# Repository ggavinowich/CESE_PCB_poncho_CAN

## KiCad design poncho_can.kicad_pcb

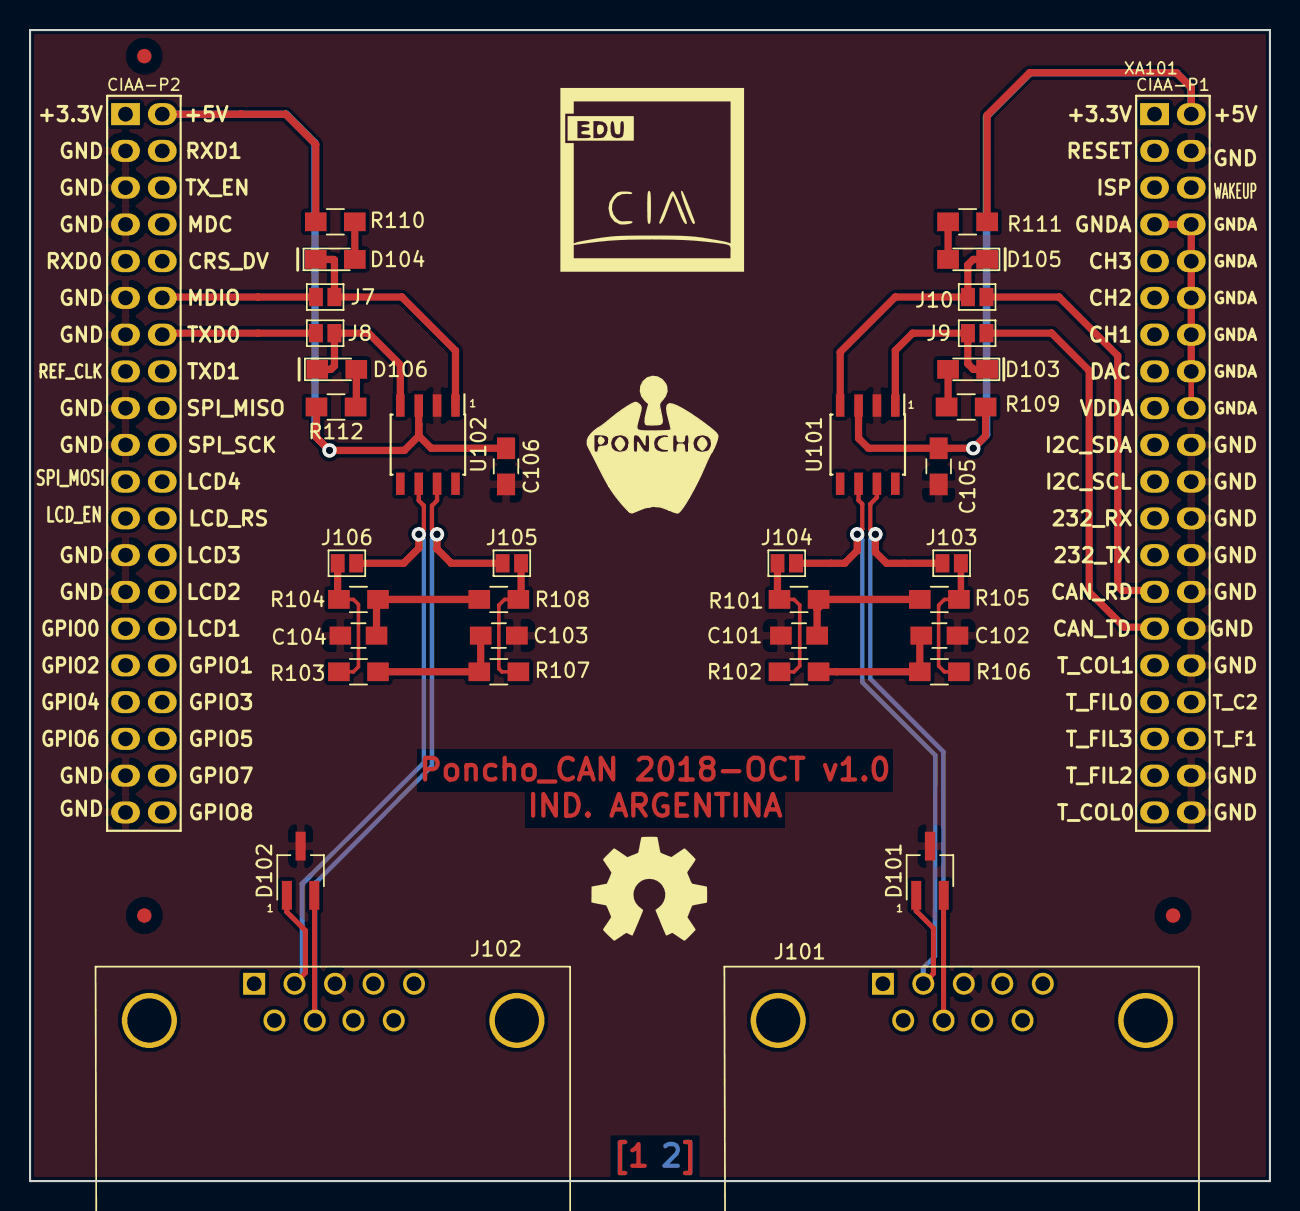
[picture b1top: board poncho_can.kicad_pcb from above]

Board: 2 copper layers, 85.7 x 79.6 mm, 41 parts (0 on the bottom side), 28 nets.

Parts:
C101, C102, C103, C104: 47n; C_0805_HandSoldering
C105, C106: 100n; C_0805_HandSoldering
D101, D102: RSB27C2; SOT-23W_Handsoldering
D103, D106: LED_RX; LED_0805_HandSoldering
D104, D105: LED_TX; LED_0805_HandSoldering
F101, F102, F103: Fiduciaria; Fiducial_1mm_Dia_2.54mm_Outer_CopperBottom
G101: Logo_OSHWA
J7, J8, J9, J10, J103, J104, J105, J106: GS2
J101, J102: DB9_Male_MountingHoles; DB9MC
R101, R102, R103, R104, R105, R106, R107, R108: 60; R_0805_HandSoldering
R109, R110, R111, R112: 270; R_0805_HandSoldering
U101, U102: TJA1051T; SOIC-8_3.9x4.9mm_Pitch1.27mm
XA101: Conn_Poncho2P_2x_20x2; Conn_Poncho_SinBorde

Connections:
+5V: C105.1, R109.2, R111.2, U101.3, XA101.2
+5VP: C106.1, R110.2, R112.2, U102.3, XA101.42
/CAN1+: D101.2, J101.7, J103.1, U101.7
/CAN1-: D101.1, J101.2, J104.2, U101.6
/CAN2+: D102.2, J102.7, J105.1, U102.7
/CAN2-: D102.1, J102.2, J106.2, U102.6
GND: C101.1, C102.2, C103.1, C104.2, C105.2, C106.2, D101.3, D102.3, J101.3, J102.3, U101.2, U102.2, XA101.4, XA101.20, XA101.22, XA101.24, XA101.26, XA101.28, XA101.30, XA101.32, XA101.38, XA101.40, XA101.43, XA101.45, XA101.47, XA101.51, XA101.53, XA101.57, XA101.59, XA101.65, XA101.67, XA101.77, XA101.79
GNDA: XA101.7, XA101.8, XA101.10, XA101.12, XA101.14, XA101.16, XA101.18
unnamed: C101.2, R101.1, R105.2
unnamed: C102.1, R102.1, R106.2
unnamed: C103.2, R103.1, R107.2
unnamed: C104.1, R104.1, R108.2
unnamed: D103.1, J9.2, U101.1
unnamed: D103.2, R109.1
unnamed: D104.1, J7.2, U102.1
unnamed: D104.2, R110.1
unnamed: D105.1, J10.2, U101.4
unnamed: D105.2, R111.1
unnamed: D106.1, J8.2, U102.4
unnamed: D106.2, R112.1
unnamed: J7.1, XA101.52
unnamed: J8.1, XA101.54
unnamed: J9.1, XA101.29
unnamed: J10.1, XA101.27
unnamed: J103.2, R105.1, R106.1
unnamed: J104.1, R101.2, R102.2
unnamed: J105.2, R107.1, R108.1
unnamed: J106.1, R103.2, R104.2

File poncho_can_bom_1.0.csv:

Component,Description,Part,References,Value,Footprint,Quantity Per PCB,Datasheet,Digikey Part Number,Manf#,Digikey#,Manf
1,,C,C105,100n,C_0805_HandSoldering,1,,311-4354-1-ND,,,
2,,C,C106,100n,C_0805_HandSoldering,1,,311-4354-1-ND,,,
3,,C,C101,47n,C_0805_HandSoldering,1,,490-7227-1-ND,,,
4,,C,C102,47n,C_0805_HandSoldering,1,,490-7227-1-ND,,,
5,,C,C103,47n,C_0805_HandSoldering,1,,490-7227-1-ND,,,
6,,C,C104,47n,C_0805_HandSoldering,1,,490-7227-1-ND,,,
7,,LED_ALT,D103,LED_RX,LED_0805_HandSoldering,1,,160-1427-1-ND,,,
8,,LED_ALT,D106,LED_RX,LED_0805_HandSoldering,1,,160-1427-1-ND,,,
9,,LED_ALT,D104,LED_TX,LED_0805_HandSoldering,1,,160-1423-1-ND,,,
10,,LED_ALT,D105,LED_TX,LED_0805_HandSoldering,1,,160-1423-1-ND,,,
11,,A00094,D101,RSB27C2,SOT-23W_Handsoldering,1,,ESD7002WTT1GOSCT-ND,,,
12,,A00094,D102,RSB27C2,SOT-23W_Handsoldering,1,,ESD7002WTT1GOSCT-ND,,,
13,,GS2,J10,GS2,GS2,1,,,,,
14,,GS2,J103,GS2,GS2,1,,,,,
15,,GS2,J104,GS2,GS2,1,,,,,
16,,GS2,J105,GS2,GS2,1,,,,,
17,,GS2,J106,GS2,GS2,1,,,,,
18,,GS2,J7,GS2,GS2,1,,,,,
19,,GS2,J8,GS2,GS2,1,,,,,
20,,GS2,J9,GS2,GS2,1,,,,,
21,,R,R109,270,R_0805_HandSoldering,1,,RMCF0805JT270RCT-ND,,,
22,,R,R110,270,R_0805_HandSoldering,1,,RMCF0805JT270RCT-ND,,,
23,,R,R111,270,R_0805_HandSoldering,1,,RMCF0805JT270RCT-ND,,,
24,,R,R112,270,R_0805_HandSoldering,1,,RMCF0805JT270RCT-ND,,,
25,,R,R101,60,R_0805_HandSoldering,1,,RMCF0805FT60R4CT-ND,,,
26,,R,R102,60,R_0805_HandSoldering,1,,RMCF0805FT60R4CT-ND,,,
27,,R,R103,60,R_0805_HandSoldering,1,,RMCF0805FT60R4CT-ND,,,
28,,R,R104,60,R_0805_HandSoldering,1,,RMCF0805FT60R4CT-ND,,,
29,,R,R105,60,R_0805_HandSoldering,1,,RMCF0805FT60R4CT-ND,,,
30,,R,R106,60,R_0805_HandSoldering,1,,RMCF0805FT60R4CT-ND,,,
31,,R,R107,60,R_0805_HandSoldering,1,,RMCF0805FT60R4CT-ND,,,
32,,R,R108,60,R_0805_HandSoldering,1,,RMCF0805FT60R4CT-ND,,,
33,,TJA1051T,U101,TJA1051T,SOIC-8_3.9x4.9mm_Pitch1.27mm,1,,568-10292-1-ND,,,
34,,TJA1051T,U102,TJA1051T,SOIC-8_3.9x4.9mm_Pitch1.27mm,1,,568-10292-1-ND,,,
35,,Conn_Poncho2P_2x_20x2,XA101,Conn_Poncho2P_2x_20x2,Conn_Poncho_SinBorde,1,,,M50-3502042,952-1387-ND,Harwin





Component Groups:,35
Component Count:,35
Fitted Components:,35
Number of PCBs:,1
Total components:,35
Schematic Version:,1.0
Schematic Date:,2018-09-21
BoM Date:,vie 16 nov 2018 10:06:49 -03
Schematic Source:,/home/cmartin/Documents/Dropbox/CESE_PCB_poncho_CAN/poncho_can.sch
KiCad Version:,Eeschema 4.0.7-e2-6376~58~ubuntu16.04.1

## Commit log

2018-09-21 Primera version del esquematico
    Todos los componentes agregados.
    Falta:
    - Reordenar todo
    - Decidir los jumpers a utilizar
2018-09-29 Agrego la proteccion en el esquematico
2018-10-04 Selección de footprints y ubicacion de componentes
2018-10-05 Ruteada una mitad.
    Falta cambiar el tamaño de la placa.
    Verificar las distancias.
    Hacer el cooper pour
2018-10-09 Improved PCB
2018-10-09 Cambio los jumpers de lugar en el esquematico y agrego leds en RX y TX
2018-10-09 Agreo la interconexion de las masas y las alimentaciones que habia borrado
2018-10-09 Agrego en el esquematico las señales de CAN como par diferencial
2018-10-09 Muevo los leds del otro lado de los jumpers de goteo
2018-10-09 Nueva colocación de los componentes
2018-10-10 Ruteo de los componentes
2018-10-12 Fin de esquematico y agrego los gerbers
2018-10-19 Agrego documentacion y aplica cambios sugeridos en la revision
2018-10-19 Rehago el fill de cobre para que quede bien indicado en la placa. Edito las comentarios en el pcb con el valor del clearence corregido
2018-10-20 Agrego texto Industria Argentina, y el fill de la mascara sobre el texto
2018-10-20 Agrego el numero de parte de Digikey para todos los componentes
2018-10-20 Agrego los modelos 3D a una carpeta local y reasigno los footprints de esa carpeta
2018-10-20 Agrego al ruta 3D de un resistor que me faltó
2018-10-30 Multiples correcciones:
    - Se removió segunda licencia en la raiz
    - Se corrigió licencia en doc/licencia
    - Se agrego la información de la licencia al rótulo del esquemático y pcb
    - Se escondieron las serigrafias de los fiduciarios
    - Se movio la serigrafia de J101 y J102
    - Se agregó la información del fabricante
2020-04-11 Cambio el esquematico para poder capturar la pantalla y usarla en la memoria
